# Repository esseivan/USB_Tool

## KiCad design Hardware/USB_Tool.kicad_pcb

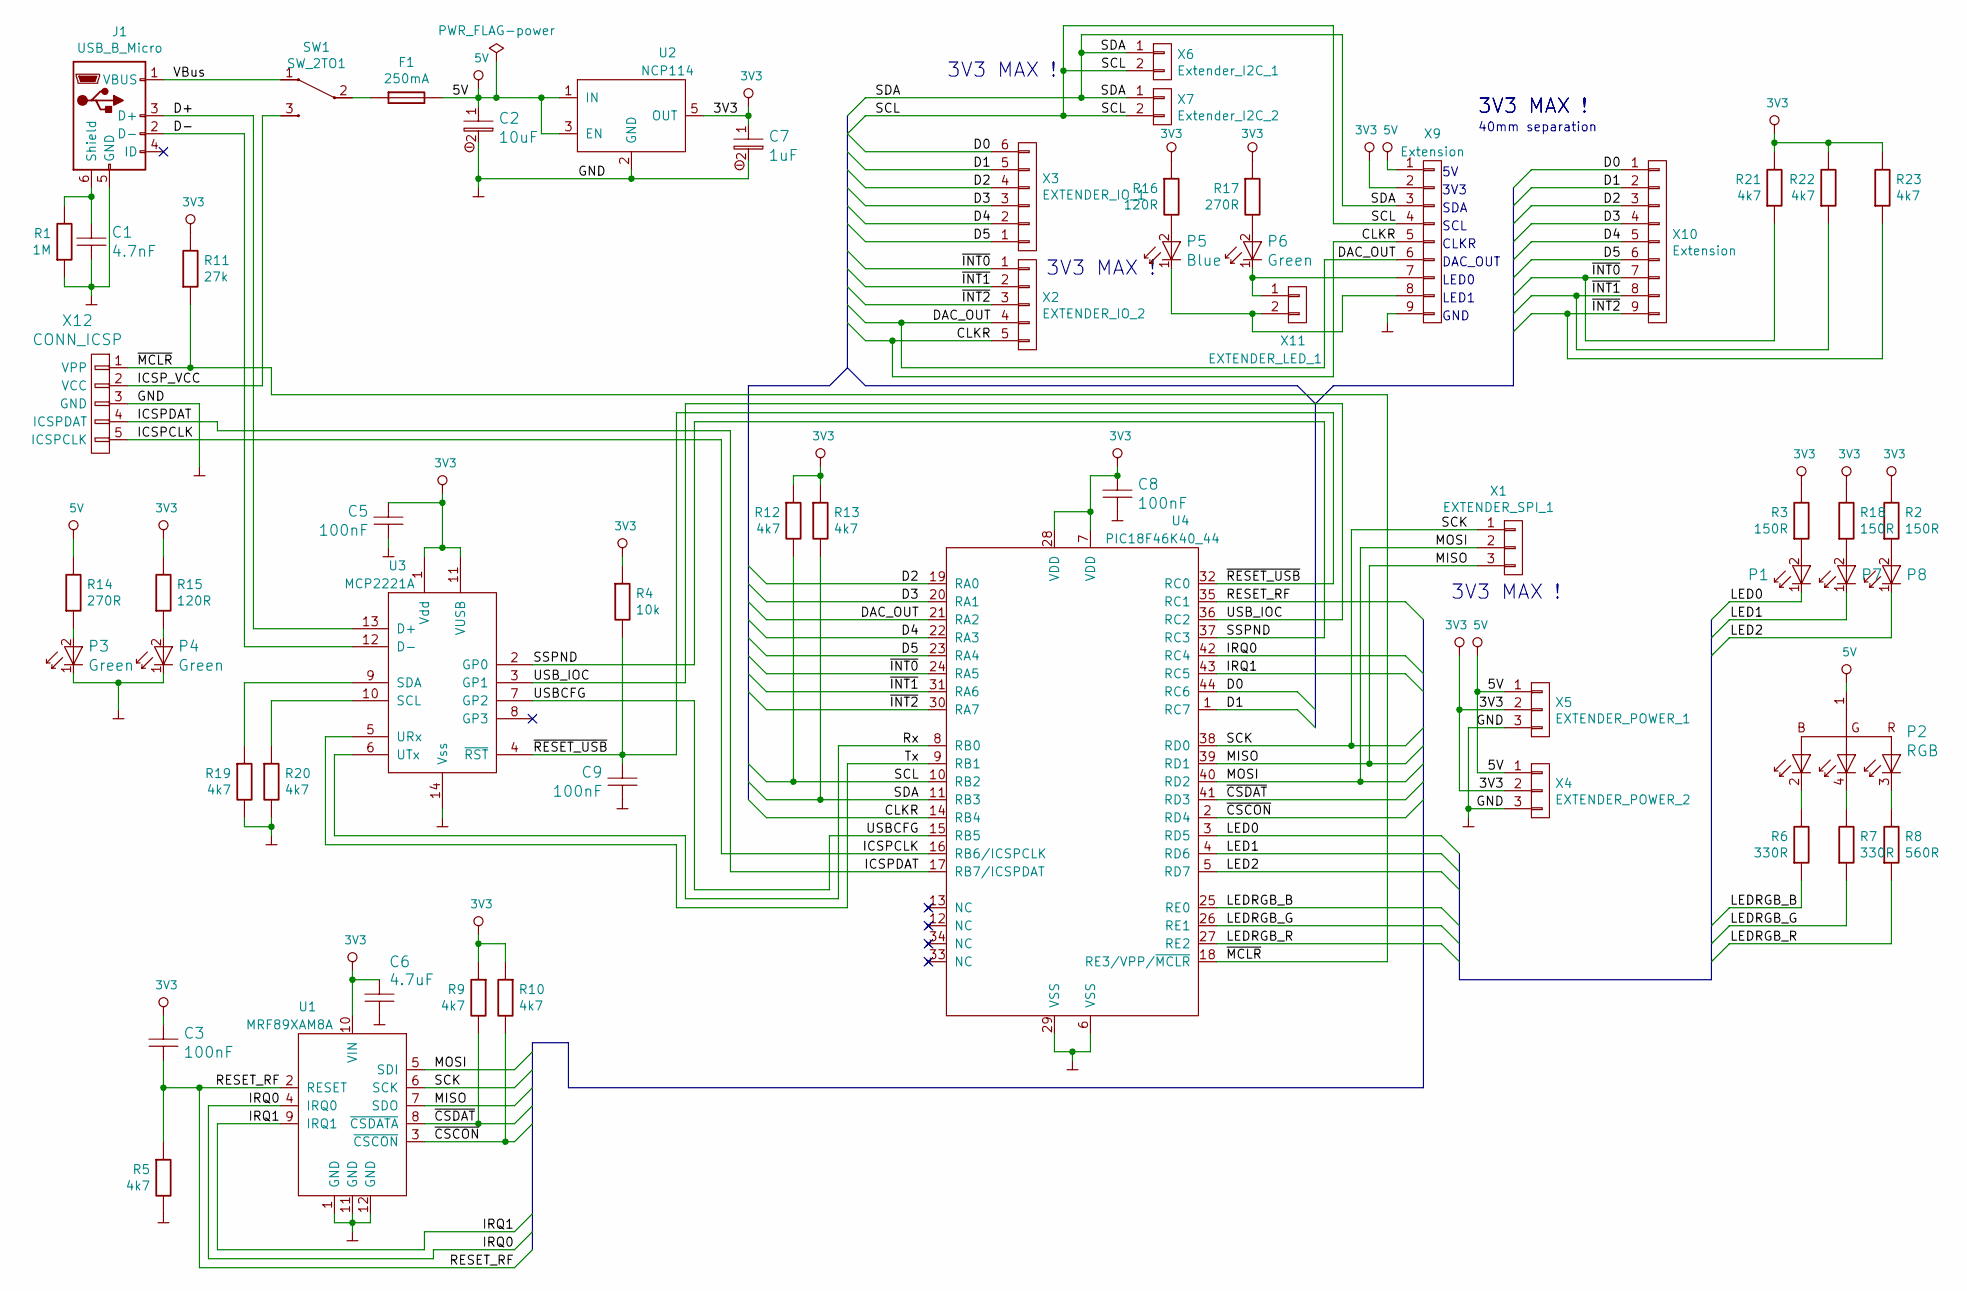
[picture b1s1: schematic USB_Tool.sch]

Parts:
C1: 4.7nF; C_0805_HandSoldering
C2: 10uF; C_0805_HandSoldering
C3, C5, C8, C9: 100nF; C_1206_HandSoldering
C6: 4.7uF; C_0805_HandSoldering
C7: 1uF; C_0805_HandSoldering
F1: 250mA; Fuse_SMD2410_HandSoldering
J1: USB_B_Micro; micro_usb
P1: RED; D_0603_HandSoldering
P2: RGB; LED_RGB_1411
P3, P4, P6, P7: Green; D_0603_HandSoldering
P5, P8: Blue; D_0805_HandSoldering
R1: 1M; R_0603_HandSoldering
R2, R3, R18: 150R; R_0603_HandSoldering
R4: 10k; R_0603_HandSoldering
R5, R9, R10, R12, R13, R19, R20, R21, R22, R23: 4k7; R_0603_HandSoldering
R6, R7: 330R; R_0603_HandSoldering
R8: 560R; R_0603_HandSoldering
R11: 27k; R_0603_HandSoldering
R14, R17: 270R; R_0603_HandSoldering
R15, R16: 120R; R_0603_HandSoldering
SW1: SW_2TO1; SLB12814
U1: MRF89XAM8A
U2: NCP114; SOT-23-5_HandSoldering
U3: MCP2221A; TSSOP-14_4.4x5mm_Pitch0.65mm
U4: PIC18F46K40_44; TQFP-44_10x10mm_Pitch0.8mm
X1: EXTENDER_SPI_1; CH_03P
X2: EXTENDER_IO_2; CH_05P
X3: EXTENDER_IO_1; CH_06P
X4: EXTENDER_POWER_2; CH_03P
X5: EXTENDER_POWER_1; CH_03P
X6: Extender_I2C_1; CH_02P
X7: Extender_I2C_2; CH_02P
X9, X10: Extension; Pin_Header_Straight_1x09_Pitch2.54mm
X11: EXTENDER_LED_1; CH_02P
X12: CONN_ICSP; Pin_Header_Straight_1x05_Pitch2.54mm

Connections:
3V3: C3.1, C5.2, C6.1, C7.1, C8.1, R2.1, R3.1, R4.2, R9.2, R10.2, R11.1, R12.2, R13.2, R15.1, R16.2, R17.2, R18.1, R21.1, R22.1, R23.1, U1.10 (VIN), U2.5 (OUT), U3.1 (Vdd), U3.11 (VUSB), U4.7 (VDD), U4.28 (VDD), X4.2, X5.2, X9.2
5V: C2.1, F1.1, P2.1 (Anode), R14.1, U2.1 (IN), U2.3 (EN), X4.1, X5.1, X9.1
/CLKR: U4.14 (RB4), X2.5, X9.5
/D0: U4.44 (RC6), X3.6, X10.1
/D1: U4.1 (RC7), X3.5, X10.2
/D2: U4.19 (RA0), X3.4, X10.3
/D3: U4.20 (RA1), X3.3, X10.4
/D4: U4.22 (RA3), X3.2, X10.5
/D5: U4.23 (RA4), X3.1, X10.6
/D+: J1.3 (D+), U3.13 (D+)
/D-: J1.2 (D-), U3.12 (D-)
/DAC_OUT: U4.21 (RA2), X2.4, X9.6
/ICSPCLK: U4.16 (RB6/ICSPCLK), X12.5 (ICSPCLK)
/ICSPDAT: U4.17 (RB7/ICSPDAT), X12.4 (ICSPDAT)
/ICSP_VCC: SW1.3 (Q2), X12.2 (VCC)
/IRQ0: U1.4 (IRQ0), U4.42 (RC4)
/IRQ1: U1.9 (IRQ1), U4.43 (RC5)
/LED0: P1.1 (Cathode), U4.3 (RD5)
/LED1: P7.1 (Cathode), U4.4 (RD6)
/LED2: P8.1 (Cathode), U4.5 (RD7)
/LEDRGB_B: R6.2, U4.25 (RE0)
/LEDRGB_G: R7.2, U4.26 (RE1)
/LEDRGB_R: R8.2, U4.27 (RE2)
/MISO: U1.7 (SDO), U4.39 (RD1), X1.3
/MOSI: U1.5 (SDI), U4.40 (RD2), X1.2
/RESET_RF: C3.2, R5.2, U1.2 (RESET), U4.35 (RC1)
/Rx: U3.6 (UTx), U4.8 (RB0)
/SCK: U1.6 (SCK), U4.38 (RD0), X1.1
/SCL: R12.1, U4.10 (RB2), X6.2, X7.2, X9.4
/SDA: R13.1, U4.11 (RB3), X6.1, X7.1, X9.3
/SSPND: U3.2 (GP0), U4.37 (RC3)
/Tx: U3.5 (URx), U4.9 (RB1)
/USBCFG: U3.7 (GP2), U4.15 (RB5)
/USB_IOC: U3.3 (GP1), U4.36 (RC2)
/VBus: J1.1 (VBUS), SW1.1 (Q1)
/~CSCON: R10.1, U1.3 (~CSCON), U4.2 (RD4)
/~CSDAT: R9.1, U1.8 (~CSDATA), U4.41 (RD3)
/~INT0: R21.2, U4.24 (RA5), X2.1, X10.7
/~INT1: R22.2, U4.31 (RA6), X2.2, X10.8
/~INT2: R23.2, U4.30 (RA7), X2.3, X10.9
/~MCLR: R11.2, U4.18 (RE3/VPP/~MCLR), X12.1 (VPP)
/~RESET_USB: C9.1, R4.1, U3.4 (~RST), U4.32 (RC0)
GND: C1.1, C2.2, C5.1, C6.2, C7.2, C8.2, C9.2, J1.5 (GND), P3.1 (Cathode), P4.1 (Cathode), R1.2, R5.1, R19.1, R20.1, U1.1 (GND), U1.11 (GND), U1.12 (GND), U2.2 (GND), U3.14 (Vss), U4.6 (VSS), U4.29 (VSS), X4.3, X5.3, X9.9, X12.3 (GND)
unnamed: C1.2, J1.6 (Shield), R1.1
unnamed: F1.2, SW1.2 (O1)
unnamed: P1.2 (Anode), R3.2
unnamed: P2.2 (BLUE), R6.1
unnamed: P2.3 (RED), R8.1
unnamed: P2.4 (GREEN), R7.1
unnamed: P3.2 (Anode), R14.2
unnamed: P4.2 (Anode), R15.2
unnamed: P5.1 (Cathode), X9.8, X11.2
unnamed: P5.2 (Anode), R16.1
unnamed: P6.1 (Cathode), X9.7, X11.1
unnamed: P6.2 (Anode), R17.1
unnamed: P7.2 (Anode), R18.2
unnamed: P8.2 (Anode), R2.2
unnamed: R19.2, U3.9 (SDA)
unnamed: R20.2, U3.10 (SCL)

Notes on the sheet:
40mm separation
3V3
SDA
SCL
GND
LED0
3V3 MAX !
CLKR
DAC_OUT
LED1

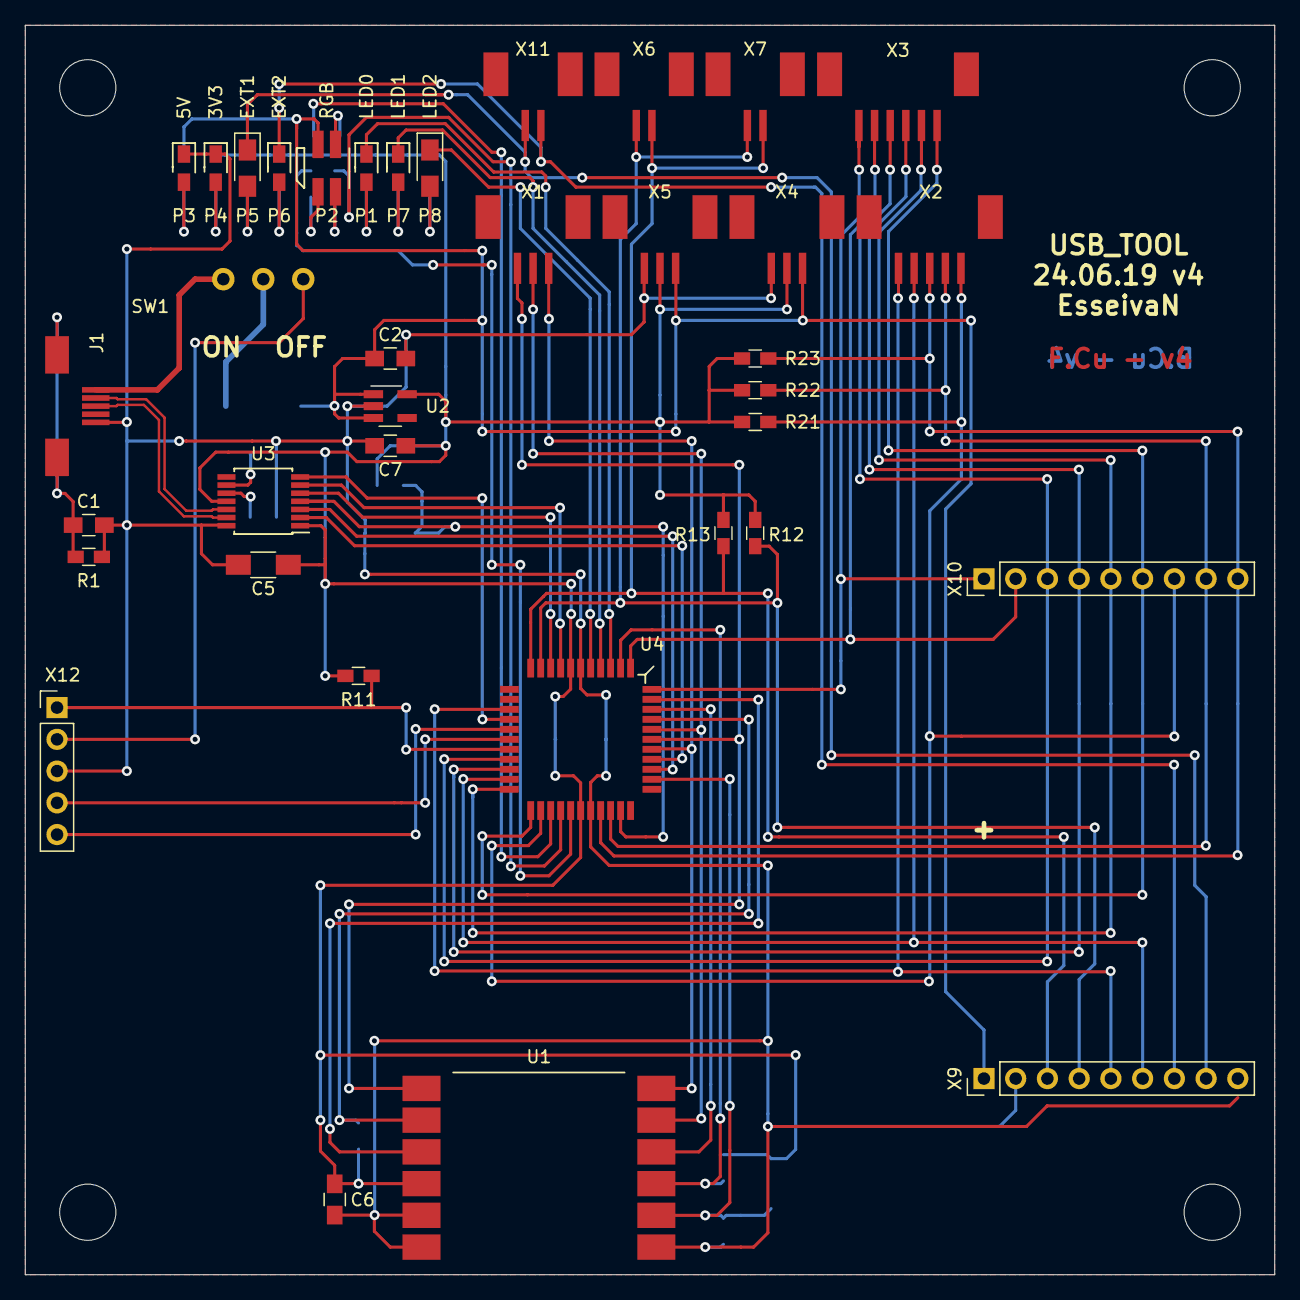
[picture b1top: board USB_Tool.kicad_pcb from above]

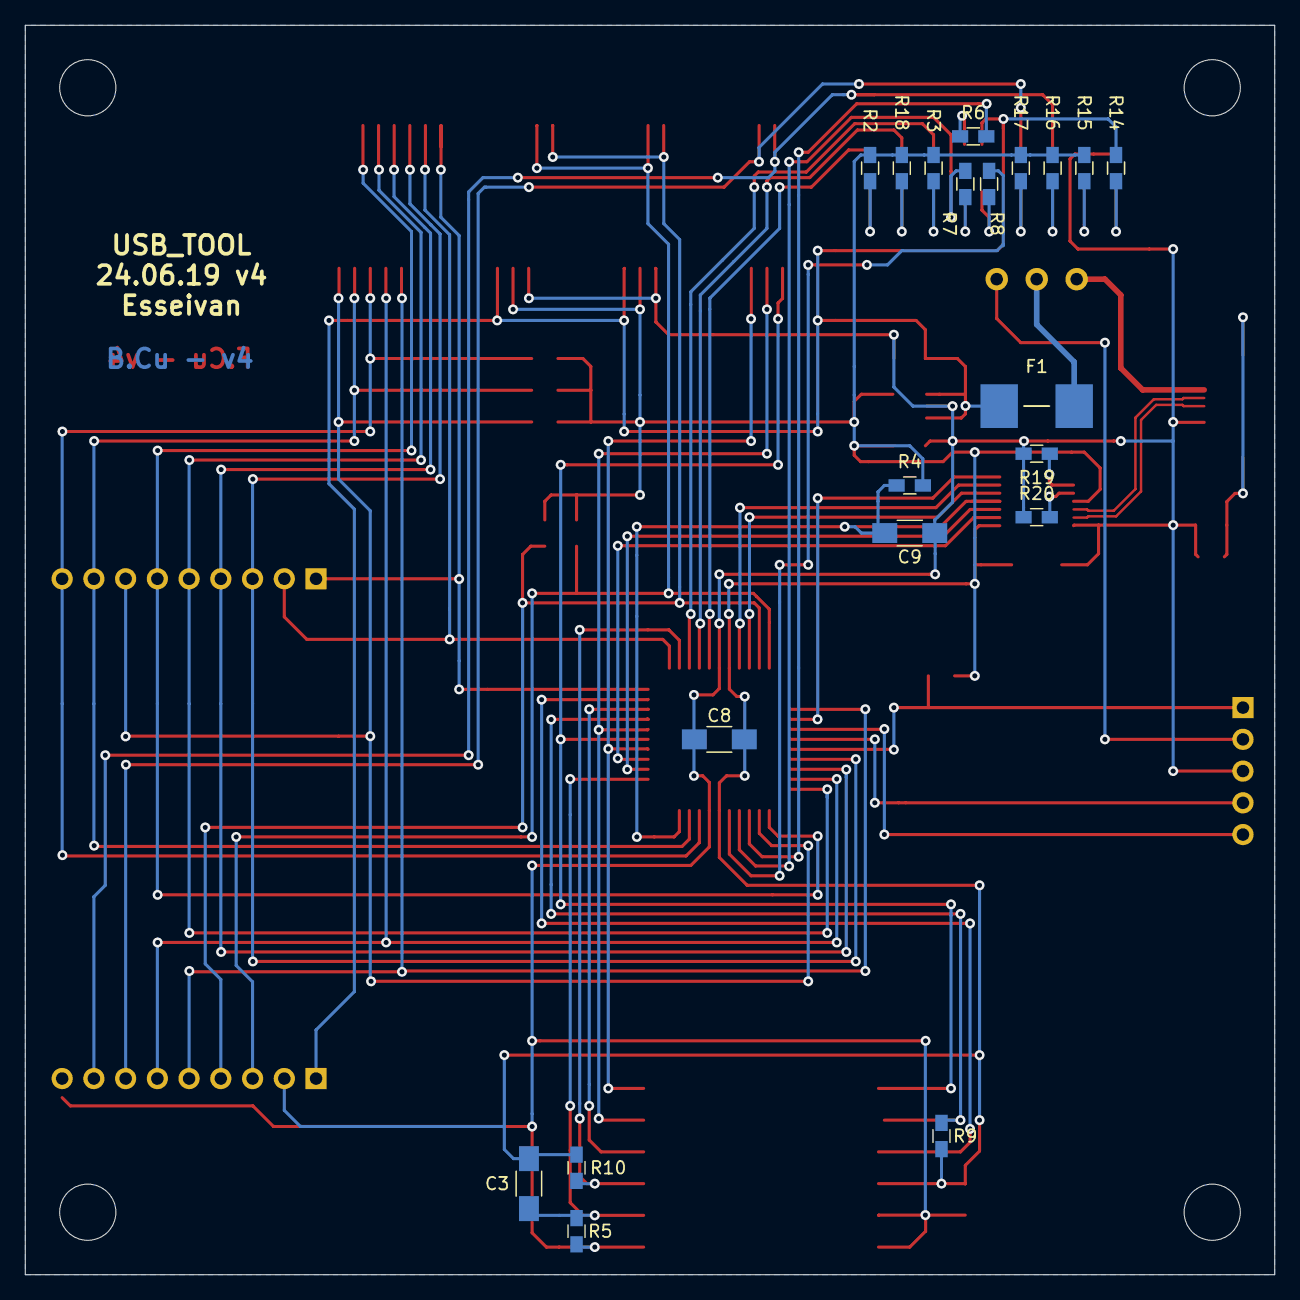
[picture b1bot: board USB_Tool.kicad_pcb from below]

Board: 2 copper layers, 100.0 x 100.0 mm, 61 parts (20 on the bottom side), 59 nets.

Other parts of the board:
PERC-4.5mm, PERC-4.5mm#2, PERC-4.5mm#3, PERC-4.5mm#4: PERC-4.5mm

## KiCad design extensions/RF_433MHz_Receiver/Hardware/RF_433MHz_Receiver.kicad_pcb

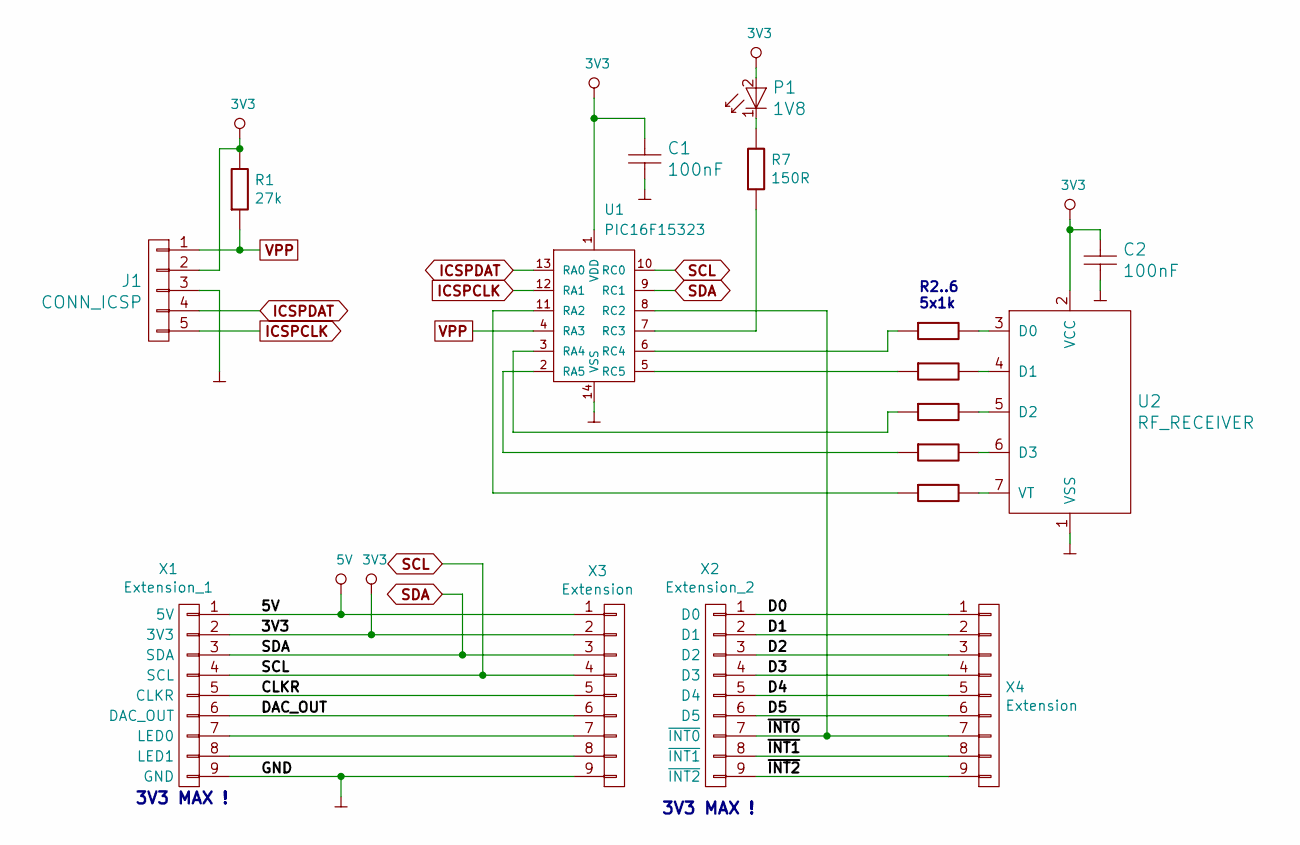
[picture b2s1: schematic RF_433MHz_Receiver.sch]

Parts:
C1, C2: 100nF; C_1206_HandSoldering
J1: CONN_ICSP; Pin_Header_Straight_1x05_Pitch2.54mm
P1: 1V8; D_0603_HandSoldering
R1: 27k; R_0603_HandSoldering
R2, R3, R4, R5, R6: 1k; R_0603_HandSoldering
R7: 150R; R_0603_HandSoldering
U1: PIC16F15323; SOIC-14
U2: RF_RECEIVER
X1: Extension_1; Pin_Header_Straight_1x09_Pitch2.54mm
X2: Extension_2; Pin_Header_Straight_1x09_Pitch2.54mm
X3, X4: Extension; Pin_Header_Straight_1x09_Pitch2.54mm

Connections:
/CLKR: X1.5 (CLKR), X3.5
/D0: X2.1 (D0), X4.1
/D1: X2.2 (D1), X4.2
/D2: X2.3 (D2), X4.3
/D3: X2.4 (D3), X4.4
/D4: X2.5 (D4), X4.5
/D5: X2.6 (D5), X4.6
/DAC_OUT: X1.6 (DAC_OUT), X3.6
/~INT0: U1.8 (RC2), X2.7 (~INT0), X4.7
/~INT1: X2.8 (~INT1), X4.8
/~INT2: X2.9 (~INT2), X4.9
GND: C1.2, C2.2, J1.3, U1.14 (VSS), U2.1 (VSS), X1.9 (GND), X3.9
ICSPCLK: J1.5, U1.12 (RA1)
ICSPDAT: J1.4, U1.13 (RA0)
unnamed: P1.1 (Cathode), R7.1
unnamed: R2.1, U2.3 (D0)
unnamed: R2.2, U1.6 (RC4)
unnamed: R3.1, U2.4 (D1)
unnamed: R3.2, U1.5 (RC5)
unnamed: R4.1, U2.5 (D2)
unnamed: R4.2, U1.3 (RA4)
unnamed: R5.1, U2.6 (D3)
unnamed: R5.2, U1.2 (RA5)
unnamed: R6.1, U2.7 (VT)
unnamed: R6.2, U1.11 (RA2)
unnamed: R7.2, U1.7 (RC3)
unnamed: X1.7 (LED0), X3.7
unnamed: X1.8 (LED1), X3.8
SCL: U1.10 (RC0), X1.4 (SCL), X3.4
SDA: U1.9 (RC1), X1.3 (SDA), X3.3
VPP: J1.1, R1.2, U1.4 (RA3)

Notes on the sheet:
R2..6 5x1k
3V3 MAX !

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
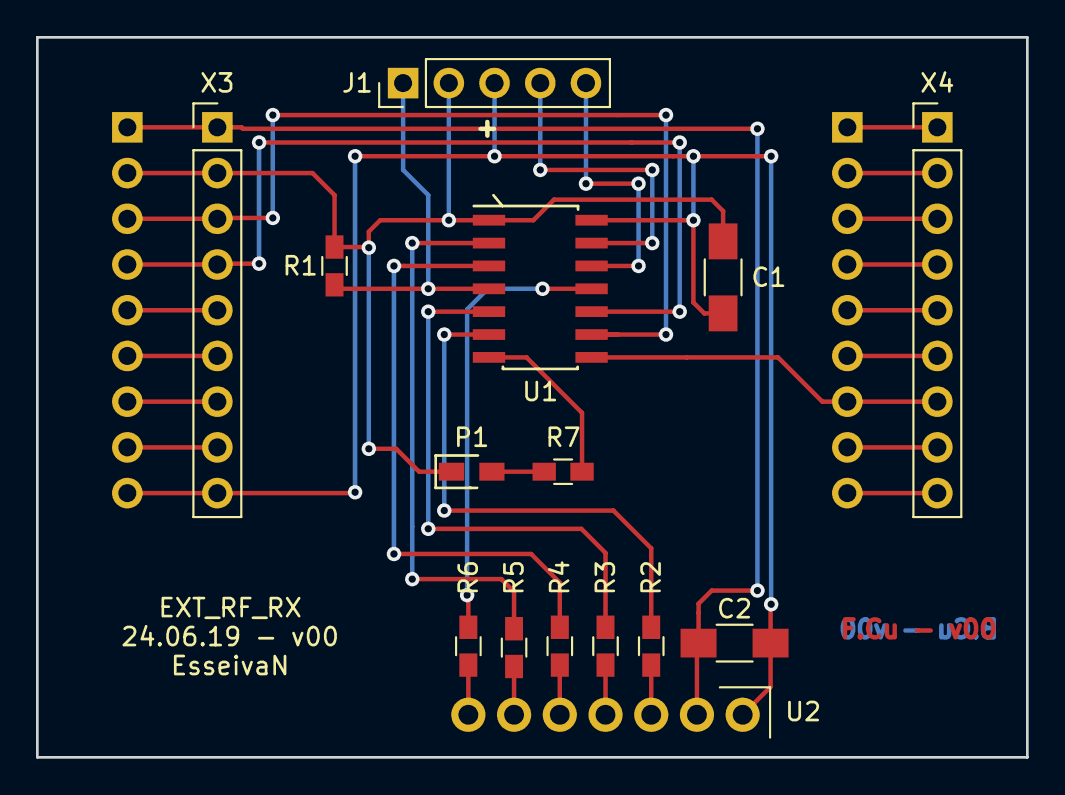
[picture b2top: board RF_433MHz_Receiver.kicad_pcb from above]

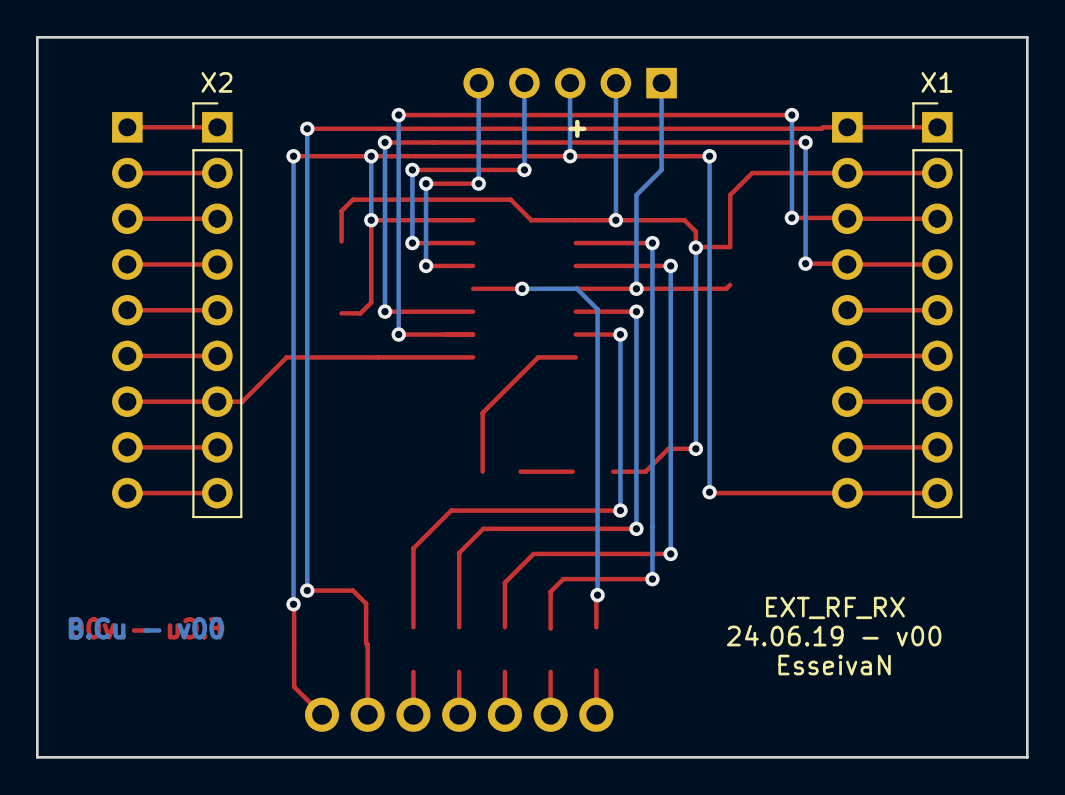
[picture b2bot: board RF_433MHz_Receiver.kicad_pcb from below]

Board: 2 copper layers, 55.0 x 40.0 mm, 17 parts (2 on the bottom side), 33 nets.

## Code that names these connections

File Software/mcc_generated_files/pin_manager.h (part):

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// get/set D2 aliases
#define D2_TRIS                 TRISAbits.TRISA0
#define D2_LAT                  LATAbits.LATA0
#define D2_PORT                 PORTAbits.RA0
#define D2_WPU                  WPUAbits.WPUA0
#define D2_OD                   ODCONAbits.ODCA0
#define D2_ANS                  ANSELAbits.ANSELA0
#define D2_SetHigh()            do { LATAbits.LATA0 = 1; } while(0)
#define D2_SetLow()             do { LATAbits.LATA0 = 0; } while(0)
#define D2_Toggle()             do { LATAbits.LATA0 = ~LATAbits.LATA0; } while(0)
#define D2_GetValue()           PORTAbits.RA0
#define D2_SetDigitalInput()    do { TRISAbits.TRISA0 = 1; } while(0)
#define D2_SetDigitalOutput()   do { TRISAbits.TRISA0 = 0; } while(0)
#define D2_SetPullup()          do { WPUAbits.WPUA0 = 1; } while(0)
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// get/set D3 aliases
#define D3_TRIS                 TRISAbits.TRISA1
#define D3_LAT                  LATAbits.LATA1
#define D3_PORT                 PORTAbits.RA1
#define D3_WPU                  WPUAbits.WPUA1
#define D3_OD                   ODCONAbits.ODCA1
#define D3_ANS                  ANSELAbits.ANSELA1
#define D3_SetHigh()            do { LATAbits.LATA1 = 1; } while(0)
#define D3_SetLow()             do { LATAbits.LATA1 = 0; } while(0)
#define D3_Toggle()             do { LATAbits.LATA1 = ~LATAbits.LATA1; } while(0)
#define D3_GetValue()           PORTAbits.RA1
#define D3_SetDigitalInput()    do { TRISAbits.TRISA1 = 1; } while(0)
#define D3_SetDigitalOutput()   do { TRISAbits.TRISA1 = 0; } while(0)
#define D3_SetPullup()          do { WPUAbits.WPUA1 = 1; } while(0)
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#define RA2_SetHigh()            do { LATAbits.LATA2 = 1; } while(0)
#define RA2_SetLow()             do { LATAbits.LATA2 = 0; } while(0)
#define RA2_Toggle()             do { LATAbits.LATA2 = ~LATAbits.LATA2; } while(0)
#define RA2_GetValue()              PORTAbits.RA2
#define RA2_SetDigitalInput()    do { TRISAbits.TRISA2 = 1; } while(0)
#define RA2_SetDigitalOutput()   do { TRISAbits.TRISA2 = 0; } while(0)
#define RA2_SetPullup()             do { WPUAbits.WPUA2 = 1; } while(0)
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// get/set D4 aliases
#define D4_TRIS                 TRISAbits.TRISA3
#define D4_LAT                  LATAbits.LATA3
#define D4_PORT                 PORTAbits.RA3
#define D4_WPU                  WPUAbits.WPUA3
#define D4_OD                   ODCONAbits.ODCA3
#define D4_ANS                  ANSELAbits.ANSELA3
#define D4_SetHigh()            do { LATAbits.LATA3 = 1; } while(0)
#define D4_SetLow()             do { LATAbits.LATA3 = 0; } while(0)
#define D4_Toggle()             do { LATAbits.LATA3 = ~LATAbits.LATA3; } while(0)
#define D4_GetValue()           PORTAbits.RA3
#define D4_SetDigitalInput()    do { TRISAbits.TRISA3 = 1; } while(0)
#define D4_SetDigitalOutput()   do { TRISAbits.TRISA3 = 0; } while(0)
#define D4_SetPullup()          do { WPUAbits.WPUA3 = 1; } while(0)
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// get/set D5 aliases
#define D5_TRIS                 TRISAbits.TRISA4
#define D5_LAT                  LATAbits.LATA4
#define D5_PORT                 PORTAbits.RA4
#define D5_WPU                  WPUAbits.WPUA4
#define D5_OD                   ODCONAbits.ODCA4
#define D5_ANS                  ANSELAbits.ANSELA4
#define D5_SetHigh()            do { LATAbits.LATA4 = 1; } while(0)
#define D5_SetLow()             do { LATAbits.LATA4 = 0; } while(0)
#define D5_Toggle()             do { LATAbits.LATA4 = ~LATAbits.LATA4; } while(0)
#define D5_GetValue()           PORTAbits.RA4
#define D5_SetDigitalInput()    do { TRISAbits.TRISA4 = 1; } while(0)
#define D5_SetDigitalOutput()   do { TRISAbits.TRISA4 = 0; } while(0)
#define D5_SetPullup()          do { WPUAbits.WPUA4 = 1; } while(0)
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#define RA5_SetHigh()            do { LATAbits.LATA5 = 1; } while(0)
#define RA5_SetLow()             do { LATAbits.LATA5 = 0; } while(0)
#define RA5_Toggle()             do { LATAbits.LATA5 = ~LATAbits.LATA5; } while(0)
#define RA5_GetValue()              PORTAbits.RA5
#define RA5_SetDigitalInput()    do { TRISAbits.TRISA5 = 1; } while(0)
#define RA5_SetDigitalOutput()   do { TRISAbits.TRISA5 = 0; } while(0)
#define RA5_SetPullup()             do { WPUAbits.WPUA5 = 1; } while(0)
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#define RA6_SetHigh()            do { LATAbits.LATA6 = 1; } while(0)
#define RA6_SetLow()             do { LATAbits.LATA6 = 0; } while(0)
#define RA6_Toggle()             do { LATAbits.LATA6 = ~LATAbits.LATA6; } while(0)
#define RA6_GetValue()              PORTAbits.RA6
#define RA6_SetDigitalInput()    do { TRISAbits.TRISA6 = 1; } while(0)
#define RA6_SetDigitalOutput()   do { TRISAbits.TRISA6 = 0; } while(0)
#define RA6_SetPullup()             do { WPUAbits.WPUA6 = 1; } while(0)
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#define RA7_SetHigh()            do { LATAbits.LATA7 = 1; } while(0)
#define RA7_SetLow()             do { LATAbits.LATA7 = 0; } while(0)
#define RA7_Toggle()             do { LATAbits.LATA7 = ~LATAbits.LATA7; } while(0)
#define RA7_GetValue()              PORTAbits.RA7
#define RA7_SetDigitalInput()    do { TRISAbits.TRISA7 = 1; } while(0)
#define RA7_SetDigitalOutput()   do { TRISAbits.TRISA7 = 0; } while(0)
#define RA7_SetPullup()             do { WPUAbits.WPUA7 = 1; } while(0)
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#define RB0_SetHigh()            do { LATBbits.LATB0 = 1; } while(0)
#define RB0_SetLow()             do { LATBbits.LATB0 = 0; } while(0)
#define RB0_Toggle()             do { LATBbits.LATB0 = ~LATBbits.LATB0; } while(0)
#define RB0_GetValue()              PORTBbits.RB0
#define RB0_SetDigitalInput()    do { TRISBbits.TRISB0 = 1; } while(0)
#define RB0_SetDigitalOutput()   do { TRISBbits.TRISB0 = 0; } while(0)
#define RB0_SetPullup()             do { WPUBbits.WPUB0 = 1; } while(0)
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#define RB1_SetHigh()            do { LATBbits.LATB1 = 1; } while(0)
#define RB1_SetLow()             do { LATBbits.LATB1 = 0; } while(0)
#define RB1_Toggle()             do { LATBbits.LATB1 = ~LATBbits.LATB1; } while(0)
#define RB1_GetValue()              PORTBbits.RB1
#define RB1_SetDigitalInput()    do { TRISBbits.TRISB1 = 1; } while(0)
#define RB1_SetDigitalOutput()   do { TRISBbits.TRISB1 = 0; } while(0)
#define RB1_SetPullup()             do { WPUBbits.WPUB1 = 1; } while(0)
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// get/set SCL aliases
#define SCL_TRIS                 TRISBbits.TRISB2
#define SCL_LAT                  LATBbits.LATB2
#define SCL_PORT                 PORTBbits.RB2
#define SCL_WPU                  WPUBbits.WPUB2
#define SCL_OD                   ODCONBbits.ODCB2
#define SCL_ANS                  ANSELBbits.ANSELB2
#define SCL_SetHigh()            do { LATBbits.LATB2 = 1; } while(0)
#define SCL_SetLow()             do { LATBbits.LATB2 = 0; } while(0)
#define SCL_Toggle()             do { LATBbits.LATB2 = ~LATBbits.LATB2; } while(0)
#define SCL_GetValue()           PORTBbits.RB2
#define SCL_SetDigitalInput()    do { TRISBbits.TRISB2 = 1; } while(0)
#define SCL_SetDigitalOutput()   do { TRISBbits.TRISB2 = 0; } while(0)
#define SCL_SetPullup()          do { WPUBbits.WPUB2 = 1; } while(0)
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// get/set SDA aliases
#define SDA_TRIS                 TRISBbits.TRISB3
#define SDA_LAT                  LATBbits.LATB3
#define SDA_PORT                 PORTBbits.RB3
#define SDA_WPU                  WPUBbits.WPUB3
#define SDA_OD                   ODCONBbits.ODCB3
#define SDA_ANS                  ANSELBbits.ANSELB3
#define SDA_SetHigh()            do { LATBbits.LATB3 = 1; } while(0)
#define SDA_SetLow()             do { LATBbits.LATB3 = 0; } while(0)
#define SDA_Toggle()             do { LATBbits.LATB3 = ~LATBbits.LATB3; } while(0)
#define SDA_GetValue()           PORTBbits.RB3
#define SDA_SetDigitalInput()    do { TRISBbits.TRISB3 = 1; } while(0)
#define SDA_SetDigitalOutput()   do { TRISBbits.TRISB3 = 0; } while(0)
#define SDA_SetPullup()          do { WPUBbits.WPUB3 = 1; } while(0)
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#define RB4_SetHigh()            do { LATBbits.LATB4 = 1; } while(0)
#define RB4_SetLow()             do { LATBbits.LATB4 = 0; } while(0)
#define RB4_Toggle()             do { LATBbits.LATB4 = ~LATBbits.LATB4; } while(0)
#define RB4_GetValue()              PORTBbits.RB4
#define RB4_SetDigitalInput()    do { TRISBbits.TRISB4 = 1; } while(0)
#define RB4_SetDigitalOutput()   do { TRISBbits.TRISB4 = 0; } while(0)
#define RB4_SetPullup()             do { WPUBbits.WPUB4 = 1; } while(0)
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// get/set USBCFG aliases
#define USBCFG_TRIS                 TRISBbits.TRISB5
#define USBCFG_LAT                  LATBbits.LATB5
#define USBCFG_PORT                 PORTBbits.RB5
#define USBCFG_WPU                  WPUBbits.WPUB5
#define USBCFG_OD                   ODCONBbits.ODCB5
#define USBCFG_ANS                  ANSELBbits.ANSELB5
#define USBCFG_SetHigh()            do { LATBbits.LATB5 = 1; } while(0)
#define USBCFG_SetLow()             do { LATBbits.LATB5 = 0; } while(0)
#define USBCFG_Toggle()             do { LATBbits.LATB5 = ~LATBbits.LATB5; } while(0)
#define USBCFG_GetValue()           PORTBbits.RB5
#define USBCFG_SetDigitalInput()    do { TRISBbits.TRISB5 = 1; } while(0)
#define USBCFG_SetDigitalOutput()   do { TRISBbits.TRISB5 = 0; } while(0)
#define USBCFG_SetPullup()          do { WPUBbits.WPUB5 = 1; } while(0)
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// get/set ISCPCLK aliases
#define ISCPCLK_TRIS                 TRISBbits.TRISB6
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
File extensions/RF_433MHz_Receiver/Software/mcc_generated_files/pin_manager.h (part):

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// get/set ICSPDAT aliases
#define ICSPDAT_TRIS                 TRISAbits.TRISA0
#define ICSPDAT_LAT                  LATAbits.LATA0
#define ICSPDAT_PORT                 PORTAbits.RA0
#define ICSPDAT_WPU                  WPUAbits.WPUA0
#define ICSPDAT_OD                   ODCONAbits.ODCA0
#define ICSPDAT_ANS                  ANSELAbits.ANSA0
#define ICSPDAT_SetHigh()            do { LATAbits.LATA0 = 1; } while(0)
#define ICSPDAT_SetLow()             do { LATAbits.LATA0 = 0; } while(0)
#define ICSPDAT_Toggle()             do { LATAbits.LATA0 = ~LATAbits.LATA0; } while(0)
#define ICSPDAT_GetValue()           PORTAbits.RA0
#define ICSPDAT_SetDigitalInput()    do { TRISAbits.TRISA0 = 1; } while(0)
#define ICSPDAT_SetDigitalOutput()   do { TRISAbits.TRISA0 = 0; } while(0)
#define ICSPDAT_SetPullup()          do { WPUAbits.WPUA0 = 1; } while(0)
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// get/set ICSPCLK aliases
#define ICSPCLK_TRIS                 TRISAbits.TRISA1
#define ICSPCLK_LAT                  LATAbits.LATA1
#define ICSPCLK_PORT                 PORTAbits.RA1
#define ICSPCLK_WPU                  WPUAbits.WPUA1
#define ICSPCLK_OD                   ODCONAbits.ODCA1
#define ICSPCLK_ANS                  ANSELAbits.ANSA1
#define ICSPCLK_SetHigh()            do { LATAbits.LATA1 = 1; } while(0)
#define ICSPCLK_SetLow()             do { LATAbits.LATA1 = 0; } while(0)
#define ICSPCLK_Toggle()             do { LATAbits.LATA1 = ~LATAbits.LATA1; } while(0)
#define ICSPCLK_GetValue()           PORTAbits.RA1
#define ICSPCLK_SetDigitalInput()    do { TRISAbits.TRISA1 = 1; } while(0)
#define ICSPCLK_SetDigitalOutput()   do { TRISAbits.TRISA1 = 0; } while(0)
#define ICSPCLK_SetPullup()          do { WPUAbits.WPUA1 = 1; } while(0)
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// get/set VT aliases
#define VT_TRIS                 TRISAbits.TRISA2
#define VT_LAT                  LATAbits.LATA2
#define VT_PORT                 PORTAbits.RA2
#define VT_WPU                  WPUAbits.WPUA2
#define VT_OD                   ODCONAbits.ODCA2
#define VT_ANS                  ANSELAbits.ANSA2
#define VT_SetHigh()            do { LATAbits.LATA2 = 1; } while(0)
#define VT_SetLow()             do { LATAbits.LATA2 = 0; } while(0)
#define VT_Toggle()             do { LATAbits.LATA2 = ~LATAbits.LATA2; } while(0)
#define VT_GetValue()           PORTAbits.RA2
#define VT_SetDigitalInput()    do { TRISAbits.TRISA2 = 1; } while(0)
#define VT_SetDigitalOutput()   do { TRISAbits.TRISA2 = 0; } while(0)
#define VT_SetPullup()          do { WPUAbits.WPUA2 = 1; } while(0)
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// get/set D2 aliases
#define D2_TRIS                 TRISAbits.TRISA4
#define D2_LAT                  LATAbits.LATA4
#define D2_PORT                 PORTAbits.RA4
#define D2_WPU                  WPUAbits.WPUA4
#define D2_OD                   ODCONAbits.ODCA4
#define D2_ANS                  ANSELAbits.ANSA4
#define D2_SetHigh()            do { LATAbits.LATA4 = 1; } while(0)
#define D2_SetLow()             do { LATAbits.LATA4 = 0; } while(0)
#define D2_Toggle()             do { LATAbits.LATA4 = ~LATAbits.LATA4; } while(0)
#define D2_GetValue()           PORTAbits.RA4
#define D2_SetDigitalInput()    do { TRISAbits.TRISA4 = 1; } while(0)
#define D2_SetDigitalOutput()   do { TRISAbits.TRISA4 = 0; } while(0)
#define D2_SetPullup()          do { WPUAbits.WPUA4 = 1; } while(0)
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// get/set D3 aliases
#define D3_TRIS                 TRISAbits.TRISA5
#define D3_LAT                  LATAbits.LATA5
#define D3_PORT                 PORTAbits.RA5
#define D3_WPU                  WPUAbits.WPUA5
#define D3_OD                   ODCONAbits.ODCA5
#define D3_ANS                  ANSELAbits.ANSA5
#define D3_SetHigh()            do { LATAbits.LATA5 = 1; } while(0)
#define D3_SetLow()             do { LATAbits.LATA5 = 0; } while(0)
#define D3_Toggle()             do { LATAbits.LATA5 = ~LATAbits.LATA5; } while(0)
#define D3_GetValue()           PORTAbits.RA5
#define D3_SetDigitalInput()    do { TRISAbits.TRISA5 = 1; } while(0)
#define D3_SetDigitalOutput()   do { TRISAbits.TRISA5 = 0; } while(0)
#define D3_SetPullup()          do { WPUAbits.WPUA5 = 1; } while(0)
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// get/set SCL aliases
#define SCL_TRIS                 TRISCbits.TRISC0
#define SCL_LAT                  LATCbits.LATC0
#define SCL_PORT                 PORTCbits.RC0
#define SCL_WPU                  WPUCbits.WPUC0
#define SCL_OD                   ODCONCbits.ODCC0
#define SCL_ANS                  ANSELCbits.ANSC0
#define SCL_SetHigh()            do { LATCbits.LATC0 = 1; } while(0)
#define SCL_SetLow()             do { LATCbits.LATC0 = 0; } while(0)
#define SCL_Toggle()             do { LATCbits.LATC0 = ~LATCbits.LATC0; } while(0)
#define SCL_GetValue()           PORTCbits.RC0
#define SCL_SetDigitalInput()    do { TRISCbits.TRISC0 = 1; } while(0)
#define SCL_SetDigitalOutput()   do { TRISCbits.TRISC0 = 0; } while(0)
#define SCL_SetPullup()          do { WPUCbits.WPUC0 = 1; } while(0)
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// get/set SDA aliases
#define SDA_TRIS                 TRISCbits.TRISC1
#define SDA_LAT                  LATCbits.LATC1
#define SDA_PORT                 PORTCbits.RC1
#define SDA_WPU                  WPUCbits.WPUC1
#define SDA_OD                   ODCONCbits.ODCC1
#define SDA_ANS                  ANSELCbits.ANSC1
#define SDA_SetHigh()            do { LATCbits.LATC1 = 1; } while(0)
#define SDA_SetLow()             do { LATCbits.LATC1 = 0; } while(0)
#define SDA_Toggle()             do { LATCbits.LATC1 = ~LATCbits.LATC1; } while(0)
#define SDA_GetValue()           PORTCbits.RC1
#define SDA_SetDigitalInput()    do { TRISCbits.TRISC1 = 1; } while(0)
#define SDA_SetDigitalOutput()   do { TRISCbits.TRISC1 = 0; } while(0)
#define SDA_SetPullup()          do { WPUCbits.WPUC1 = 1; } while(0)
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// get/set INT0 aliases
#define INT0_TRIS                 TRISCbits.TRISC2
#define INT0_LAT                  LATCbits.LATC2
#define INT0_PORT                 PORTCbits.RC2
#define INT0_WPU                  WPUCbits.WPUC2
#define INT0_OD                   ODCONCbits.ODCC2
#define INT0_ANS                  ANSELCbits.ANSC2
#define INT0_SetHigh()            do { LATCbits.LATC2 = 1; } while(0)
#define INT0_SetLow()             do { LATCbits.LATC2 = 0; } while(0)
#define INT0_Toggle()             do { LATCbits.LATC2 = ~LATCbits.LATC2; } while(0)
#define INT0_GetValue()           PORTCbits.RC2
#define INT0_SetDigitalInput()    do { TRISCbits.TRISC2 = 1; } while(0)
#define INT0_SetDigitalOutput()   do { TRISCbits.TRISC2 = 0; } while(0)
#define INT0_SetPullup()          do { WPUCbits.WPUC2 = 1; } while(0)
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// get/set LED aliases
#define LED_TRIS                 TRISCbits.TRISC3
#define LED_LAT                  LATCbits.LATC3
#define LED_PORT                 PORTCbits.RC3
#define LED_WPU                  WPUCbits.WPUC3
#define LED_OD                   ODCONCbits.ODCC3
#define LED_ANS                  ANSELCbits.ANSC3
#define LED_SetHigh()            do { LATCbits.LATC3 = 1; } while(0)
#define LED_SetLow()             do { LATCbits.LATC3 = 0; } while(0)
#define LED_Toggle()             do { LATCbits.LATC3 = ~LATCbits.LATC3; } while(0)
#define LED_GetValue()           PORTCbits.RC3
#define LED_SetDigitalInput()    do { TRISCbits.TRISC3 = 1; } while(0)
#define LED_SetDigitalOutput()   do { TRISCbits.TRISC3 = 0; } while(0)
#define LED_SetPullup()          do { WPUCbits.WPUC3 = 1; } while(0)
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// get/set D0 aliases
#define D0_TRIS                 TRISCbits.TRISC4
#define D0_LAT                  LATCbits.LATC4
#define D0_PORT                 PORTCbits.RC4
#define D0_WPU                  WPUCbits.WPUC4
#define D0_OD                   ODCONCbits.ODCC4
#define D0_ANS                  ANSELCbits.ANSC4
#define D0_SetHigh()            do { LATCbits.LATC4 = 1; } while(0)
#define D0_SetLow()             do { LATCbits.LATC4 = 0; } while(0)
#define D0_Toggle()             do { LATCbits.LATC4 = ~LATCbits.LATC4; } while(0)
#define D0_GetValue()           PORTCbits.RC4
#define D0_SetDigitalInput()    do { TRISCbits.TRISC4 = 1; } while(0)
#define D0_SetDigitalOutput()   do { TRISCbits.TRISC4 = 0; } while(0)
#define D0_SetPullup()          do { WPUCbits.WPUC4 = 1; } while(0)
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// get/set D1 aliases
#define D1_TRIS                 TRISCbits.TRISC5
#define D1_LAT                  LATCbits.LATC5
#define D1_PORT                 PORTCbits.RC5
#define D1_WPU                  WPUCbits.WPUC5
#define D1_OD                   ODCONCbits.ODCC5
#define D1_ANS                  ANSELCbits.ANSC5
#define D1_SetHigh()            do { LATCbits.LATC5 = 1; } while(0)
#define D1_SetLow()             do { LATCbits.LATC5 = 0; } while(0)
#define D1_Toggle()             do { LATCbits.LATC5 = ~LATCbits.LATC5; } while(0)
#define D1_GetValue()           PORTCbits.RC5
#define D1_SetDigitalInput()    do { TRISCbits.TRISC5 = 1; } while(0)
#define D1_SetDigitalOutput()   do { TRISCbits.TRISC5 = 0; } while(0)
#define D1_SetPullup()          do { WPUCbits.WPUC5 = 1; } while(0)
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
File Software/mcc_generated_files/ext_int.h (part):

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 */
/**
  @Summary
    Interrupt Service Routine for EXT_INT0 - INT0 pin

  @Description
    This ISR will execute whenever the signal on the INT0 pin will transition to the preconfigured state.
    
  @Preconditions
    EXT_INT intializer called
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
/**
  @Summary
    Interrupt Handler Setter for EXT_INT0 - INT0 pin

  @Description
    Allows selecting an interrupt handler for EXT_INT0 - INT0 at application runtime
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
/**
  @Summary
    Dynamic Interrupt Handler for EXT_INT0 - INT0 pin

  @Description
    This is the dynamic interrupt handler to be used together with the INT0_SetInterruptHandler() method.
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
/**
  @Summary
    Default Interrupt Handler for EXT_INT0 - INT0 pin

  @Description
    This is a predefined interrupt handler to be used together with the INT0_SetInterruptHandler() method.
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void INT0_DefaultInterruptHandler(void);
/**
  @Summary
    Interrupt Service Routine for EXT_INT1 - INT1 pin

  @Description
    This ISR will execute whenever the signal on the INT1 pin will transition to the preconfigured state.
    
  @Preconditions
    EXT_INT intializer called
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
/**
  @Summary
    Interrupt Handler Setter for EXT_INT1 - INT1 pin

  @Description
    Allows selecting an interrupt handler for EXT_INT1 - INT1 at application runtime
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
/**
  @Summary
    Dynamic Interrupt Handler for EXT_INT1 - INT1 pin

  @Description
    This is the dynamic interrupt handler to be used together with the INT1_SetInterruptHandler() method.
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
/**
  @Summary
    Default Interrupt Handler for EXT_INT1 - INT1 pin

  @Description
    This is a predefined interrupt handler to be used together with the INT1_SetInterruptHandler() method.
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void INT1_DefaultInterruptHandler(void);
/**
  @Summary
    Interrupt Service Routine for EXT_INT2 - INT2 pin

  @Description
    This ISR will execute whenever the signal on the INT2 pin will transition to the preconfigured state.
    
  @Preconditions
    EXT_INT intializer called
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
/**
  @Summary
    Interrupt Handler Setter for EXT_INT2 - INT2 pin

  @Description
    Allows selecting an interrupt handler for EXT_INT2 - INT2 at application runtime
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
/**
  @Summary
    Dynamic Interrupt Handler for EXT_INT2 - INT2 pin

  @Description
    This is the dynamic interrupt handler to be used together with the INT2_SetInterruptHandler() method.
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
/**
  @Summary
    Default Interrupt Handler for EXT_INT2 - INT2 pin

  @Description
    This is a predefined interrupt handler to be used together with the INT2_SetInterruptHandler() method.
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
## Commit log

2019-04-14 Origin upload
2019-04-14 First part done, usb to spi
2019-04-17 update TBD
2019-04-17 added rf module
    3v3 ldo
    switch power
2019-04-17 Updated TBD
2019-04-17 Merged libraries and fixed errors
2019-04-19 Fixed merge rescue
2019-04-20 Cleanup and software project created
2019-05-01 v0 Completed
2019-05-08 v1
    selectable mcu & rf transceiver power voltage
2019-05-08 mod v0 to v1
2019-05-08 Don't ignore mplab
2019-05-10 added pcb picture
2019-05-22 Issues fix
2019-05-22 v2
    Changed led from PORTB to PORTE
    Changed IRQ0,1 & CS_EXIT to PORTB for IOC
2019-05-22 Updated silkscreen
    + mod (0/1) to 2
2019-06-17 Some fix
2019-06-23 v4 updated
2019-06-24 v4 final
2019-07-04 software update
2019-07-08 OOK kinda working
2019-07-08 ook *kinda working again
    Values not good, reception ok
2019-07-30 trying to get correct data

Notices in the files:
Software/mcc_generated_files/ext_int.h:
(c) 2018 Microchip Technology Inc. and its subsidiaries.
